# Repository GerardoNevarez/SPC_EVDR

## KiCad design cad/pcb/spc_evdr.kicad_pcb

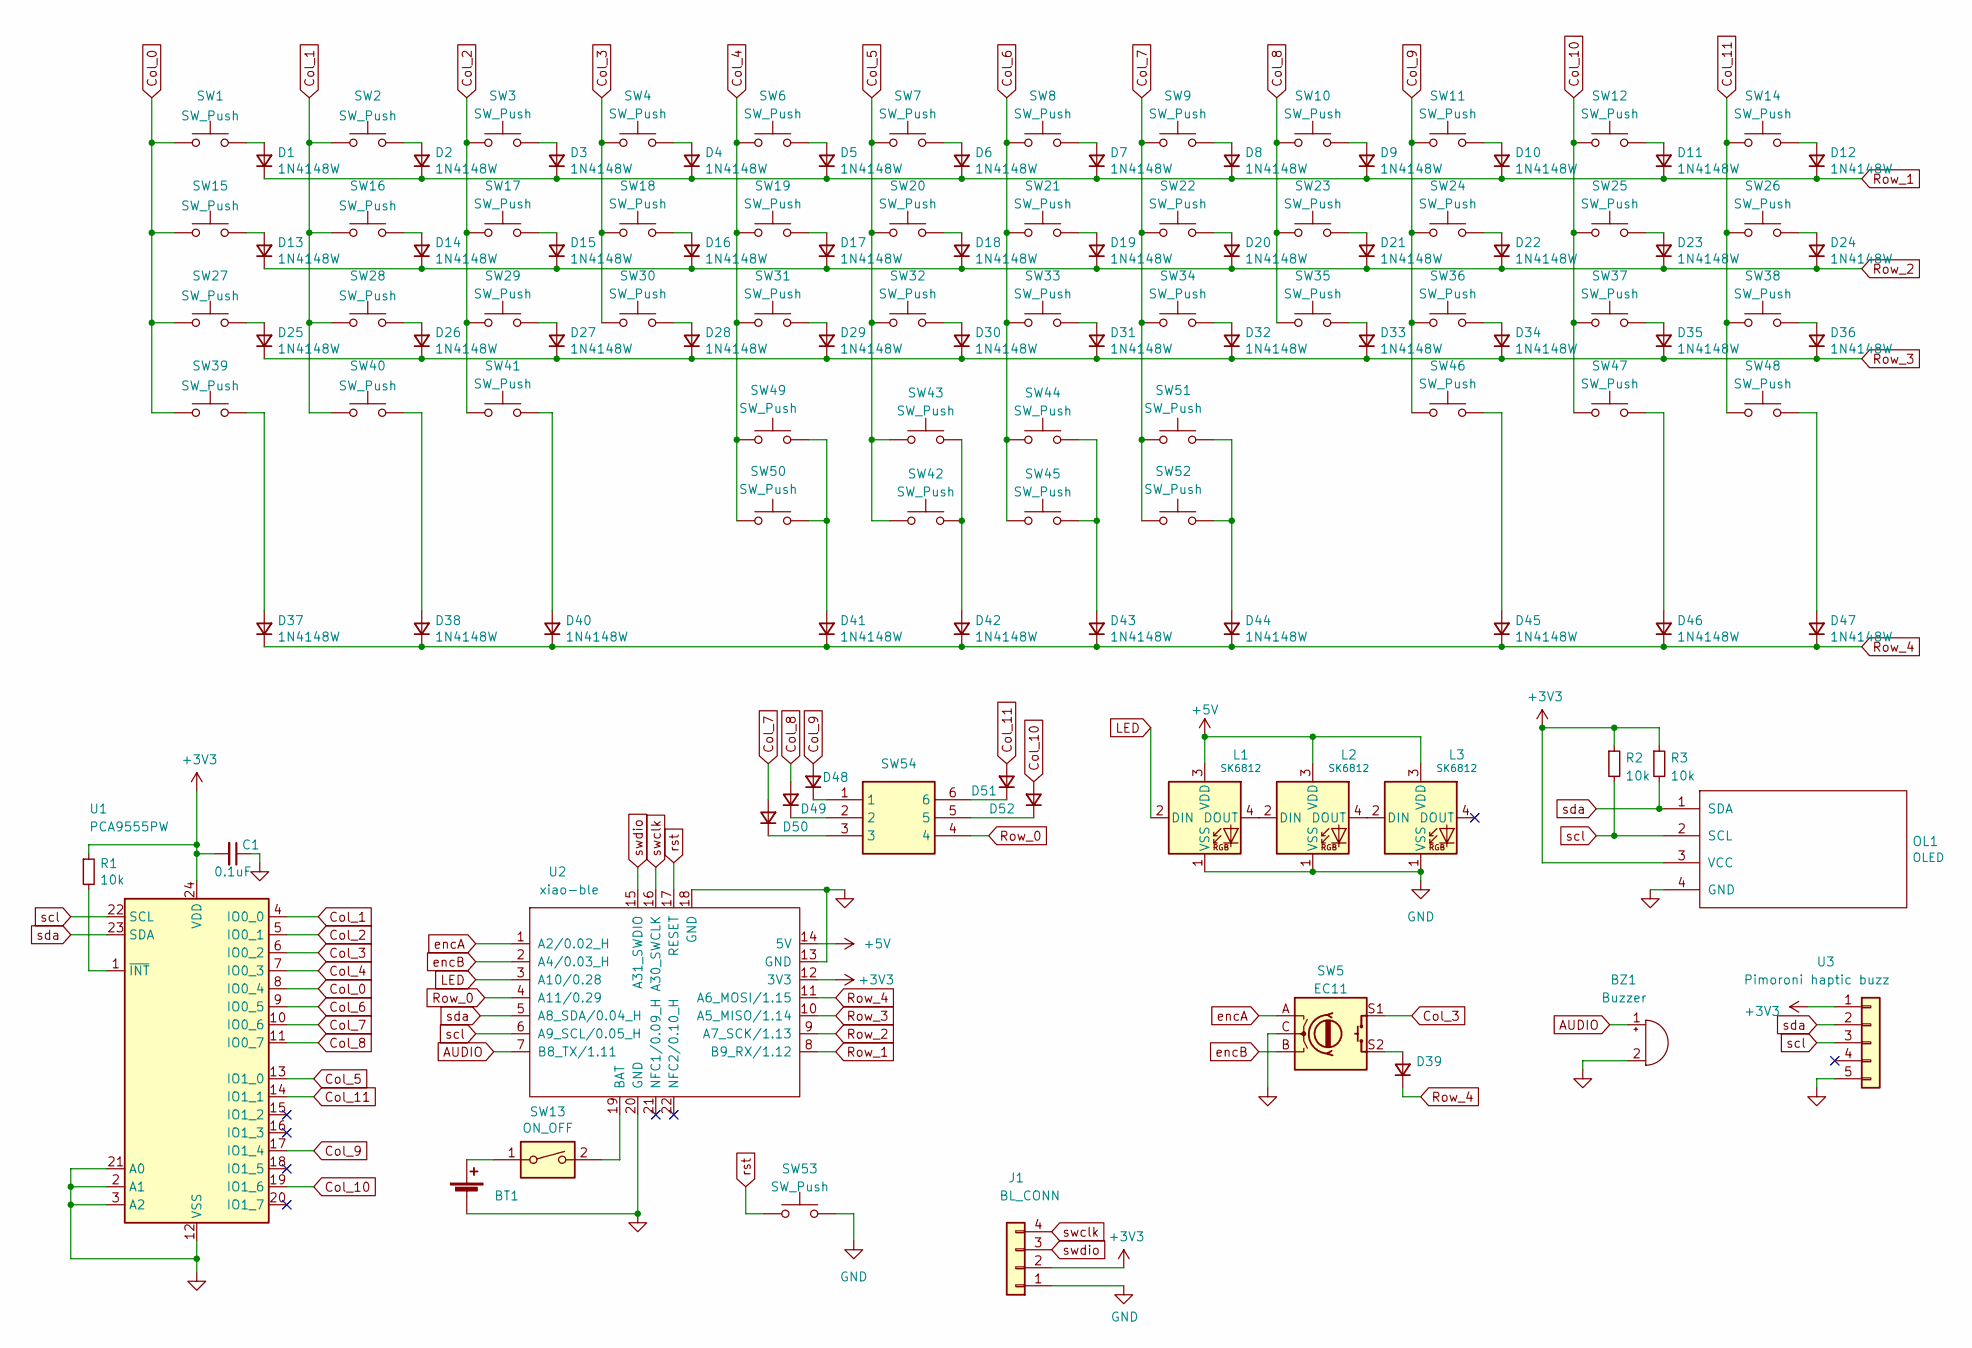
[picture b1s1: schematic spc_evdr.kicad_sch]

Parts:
BT1: Battery_Cell; Molex_PicoBlade_53048-0210_1x02_P1.25mm_Horizontal
BZ1: Buzzer; Buzzer_Mallory_AST1109MLTRQ_reversible
C1: 0.1uF; C_0805_2012Metric
D1, D2, D3, D4, D5, D6, D7, D8, D9, D10, D11, D12, D13, D14, D15, D16, D17, D18, D19, D20, D21, D22, D23, D24, D25, D26, D27, D28, D29, D30, D31, D32, D33, D34, D35, D36, D37, D38, D39, D40, D41, D42, D43, D44, D45, D46, D47, D48, D49, D50, D51, D52: 1N4148W; D_SOD-123
J1: BL_CONN; PinHeader_1x04_P2.54mm_Vertical
L1, L2, L3: SK6812; LED_SK6812_PLCC4_5.0x5.0mm_P3.2mm
OL1: OLED; OLED_1side
R1, R2, R3: 10k; R_0805_2012Metric
SW1, SW2, SW3, SW4, SW6, SW7, SW8, SW9, SW10, SW11, SW12, SW14, SW15, SW16, SW17, SW18, SW19, SW20, SW21, SW22, SW23, SW24, SW25, SW26, SW27, SW28, SW29, SW30, SW31, SW32, SW33, SW34, SW35, SW36, SW37, SW38, SW39, SW40, SW41, SW46, SW47: SW_Push; CherryMX_Hotswap
SW5: EC11; RotaryEncoder_Alps_EC11E-Switch_Vertical_H20mm-keebio_modif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
SW13: ON_OFF; switch_MSK-12C02_smd
SW42, SW45, SW49, SW51: SW_Push; Inv_CherryMX_Hotswap_1.25u
SW43, SW44, SW50, SW52: SW_Push; Inv_CherryMX_Hotswap_1.5u
SW48: SW_Push; CherryMX_1u
SW53: SW_Push; Micro_Push_Button_3x6x2.5mm
SW54: SKQUCAA010; Mouser Part Number 688-SKQUCA
U1: PCA9555PW; TSSOP-24_4.4x7.8mm_P0.65mm
U2: xiao-ble; xiao-ble-smd-cutout
U3: Pimoroni haptic buzz; Pimoroni Haptic Buzz DRV2605L Driver

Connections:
+3V3: C1.2, J1.2, OL1.3 (VCC), R1.1, R2.1, R3.1, U1.24 (VDD), U2.12 (3V3), U3.1
+5V: L1.3 (VDD), L2.3 (VDD), L3.3 (VDD), U2.14 (5V)
AUDIO: BZ1.1 (-), U2.7 (B8_TX/1.11)
Col_0: SW1.1, SW15.1, SW27.1, SW39.1, U1.8 (IO0_4)
Col_1: SW2.1, SW16.1, SW28.1, SW40.1, U1.4 (IO0_0)
Col_2: SW3.1, SW17.1, SW29.1, SW41.1, U1.5 (IO0_1)
Col_3: SW4.1, SW5.S1, SW18.1, SW30.1, U1.6 (IO0_2)
Col_4: SW6.1, SW19.1, SW31.1, SW49.1, SW50.1, U1.7 (IO0_3)
Col_5: SW7.1, SW20.1, SW32.1, SW42.1, SW43.1, U1.13 (IO1_0)
Col_6: SW8.1, SW21.1, SW33.1, SW44.1, SW45.1, U1.9 (IO0_5)
Col_7: D50.2 (A), SW9.1, SW22.1, SW34.1, SW51.1, SW52.1, U1.10 (IO0_6)
Col_8: D49.2 (A), SW10.1, SW23.1, SW35.1, U1.11 (IO0_7)
Col_9: D48.2 (A), SW11.1, SW24.1, SW36.1, SW46.1, U1.17 (IO1_4)
Col_10: D52.2 (A), SW12.1, SW25.1, SW37.1, SW47.1, U1.19 (IO1_6)
Col_11: D51.2 (A), SW14.1, SW26.1, SW38.1, SW48.1, U1.14 (IO1_1)
GND: BT1.2 (-), BZ1.2 (+), C1.1, J1.1, L1.1 (VSS), L2.1 (VSS), L3.1 (VSS), OL1.4 (GND), SW5.C, SW53.2, U1.2 (A1), U1.3 (A2), U1.12 (VSS), U1.21 (A0), U2.13 (GND), U2.18 (GND), U2.20 (GND), U3.5
LED: L1.2 (DIN), U2.3 (A10/0.28)
unnamed: BT1.1 (+), SW13.1
unnamed: D1.2 (A), SW1.2
unnamed: D2.2 (A), SW2.2
unnamed: D3.2 (A), SW3.2
unnamed: D4.2 (A), SW4.2
unnamed: D5.2 (A), SW6.2
unnamed: D6.2 (A), SW7.2
unnamed: D7.2 (A), SW8.2
unnamed: D8.2 (A), SW9.2
unnamed: D9.2 (A), SW10.2
unnamed: D10.2 (A), SW11.2
unnamed: D11.2 (A), SW12.2
unnamed: D12.2 (A), SW14.2
unnamed: D13.2 (A), SW15.2
unnamed: D14.2 (A), SW16.2
unnamed: D15.2 (A), SW17.2
unnamed: D16.2 (A), SW18.2
unnamed: D17.2 (A), SW19.2
unnamed: D18.2 (A), SW20.2
unnamed: D19.2 (A), SW21.2
unnamed: D20.2 (A), SW22.2
unnamed: D21.2 (A), SW23.2
unnamed: D22.2 (A), SW24.2
unnamed: D23.2 (A), SW25.2
unnamed: D24.2 (A), SW26.2
unnamed: D25.2 (A), SW27.2
unnamed: D26.2 (A), SW28.2
unnamed: D27.2 (A), SW29.2
unnamed: D28.2 (A), SW30.2
unnamed: D29.2 (A), SW31.2
unnamed: D30.2 (A), SW32.2
unnamed: D31.2 (A), SW33.2
unnamed: D32.2 (A), SW34.2
unnamed: D33.2 (A), SW35.2
unnamed: D34.2 (A), SW36.2
unnamed: D35.2 (A), SW37.2
unnamed: D36.2 (A), SW38.2
unnamed: D37.2 (A), SW39.2
unnamed: D38.2 (A), SW40.2
unnamed: D39.2 (A), SW5.S2
unnamed: D40.2 (A), SW41.2
unnamed: D41.2 (A), SW49.2, SW50.2
unnamed: D42.2 (A), SW42.2, SW43.2
unnamed: D43.2 (A), SW44.2, SW45.2
unnamed: D44.2 (A), SW51.2, SW52.2
unnamed: D45.2 (A), SW46.2
unnamed: D46.2 (A), SW47.2
unnamed: D47.2 (A), SW48.2
unnamed: D48.1 (K), SW54.1
unnamed: D49.1 (K), SW54.2
unnamed: D50.1 (K), SW54.3
unnamed: D51.1 (K), SW54.6
unnamed: D52.1 (K), SW54.5
unnamed: L1.4 (DOUT), L2.2 (DIN)
unnamed: L2.4 (DOUT), L3.2 (DIN)
unnamed: R1.2, U1.1 (~INT)
unnamed: SW13.2, U2.19 (BAT)
Row_0: SW54.4, U2.4 (A11/0.29)
Row_1: D1.1 (K), D2.1 (K), D3.1 (K), D4.1 (K), D5.1 (K), D6.1 (K), D7.1 (K), D8.1 (K), D9.1 (K), D10.1 (K), D11.1 (K), D12.1 (K), U2.8 (B9_RX/1.12)
Row_2: D13.1 (K), D14.1 (K), D15.1 (K), D16.1 (K), D17.1 (K), D18.1 (K), D19.1 (K), D20.1 (K), D21.1 (K), D22.1 (K), D23.1 (K), D24.1 (K), U2.9 (A7_SCK/1.13)
Row_3: D25.1 (K), D26.1 (K), D27.1 (K), D28.1 (K), D29.1 (K), D30.1 (K), D31.1 (K), D32.1 (K), D33.1 (K), D34.1 (K), D35.1 (K), D36.1 (K), U2.10 (A5_MISO/1.14)
Row_4: D37.1 (K), D38.1 (K), D39.1 (K), D40.1 (K), D41.1 (K), D42.1 (K), D43.1 (K), D44.1 (K), D45.1 (K), D46.1 (K), D47.1 (K), U2.11 (A6_MOSI/1.15)
encA: SW5.A, U2.1 (A2/0.02_H)
encB: SW5.B, U2.2 (A4/0.03_H)
rst: SW53.1, U2.17 (RESET)
scl: OL1.2 (SCL), R2.2, U1.22 (SCL), U2.6 (A9_SCL/0.05_H), U3.3
sda: OL1.1 (SDA), R3.2, U1.23 (SDA), U2.5 (A8_SDA/0.04_H), U3.2
swclk: J1.4, U2.16 (A30_SWCLK)
swdio: J1.3, U2.15 (A31_SWDIO)

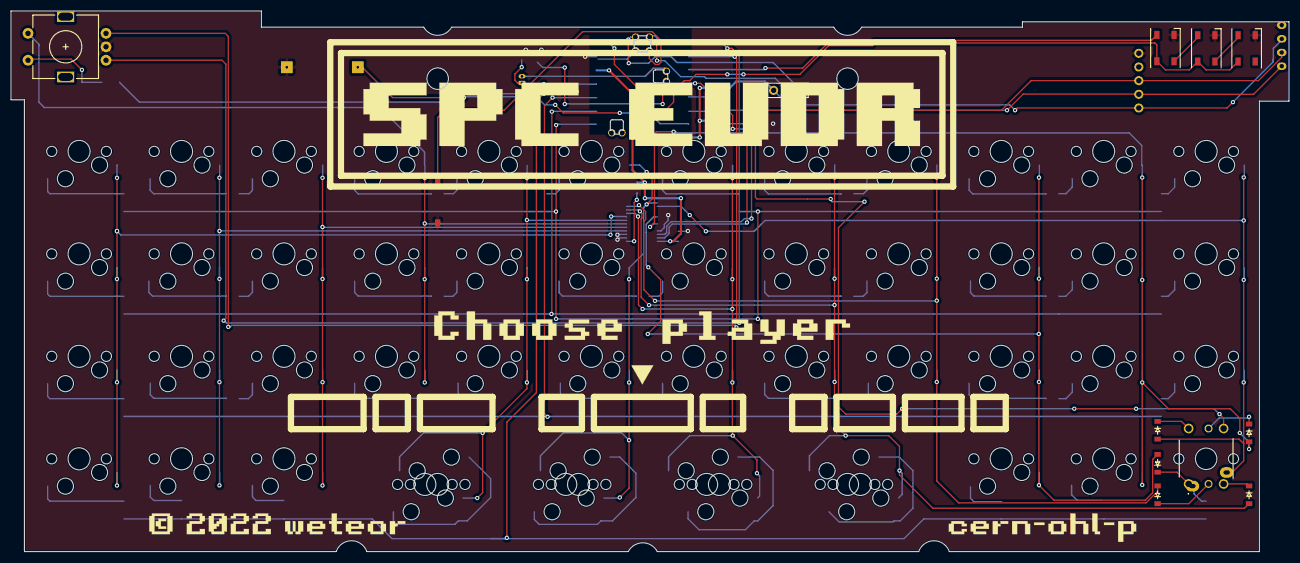
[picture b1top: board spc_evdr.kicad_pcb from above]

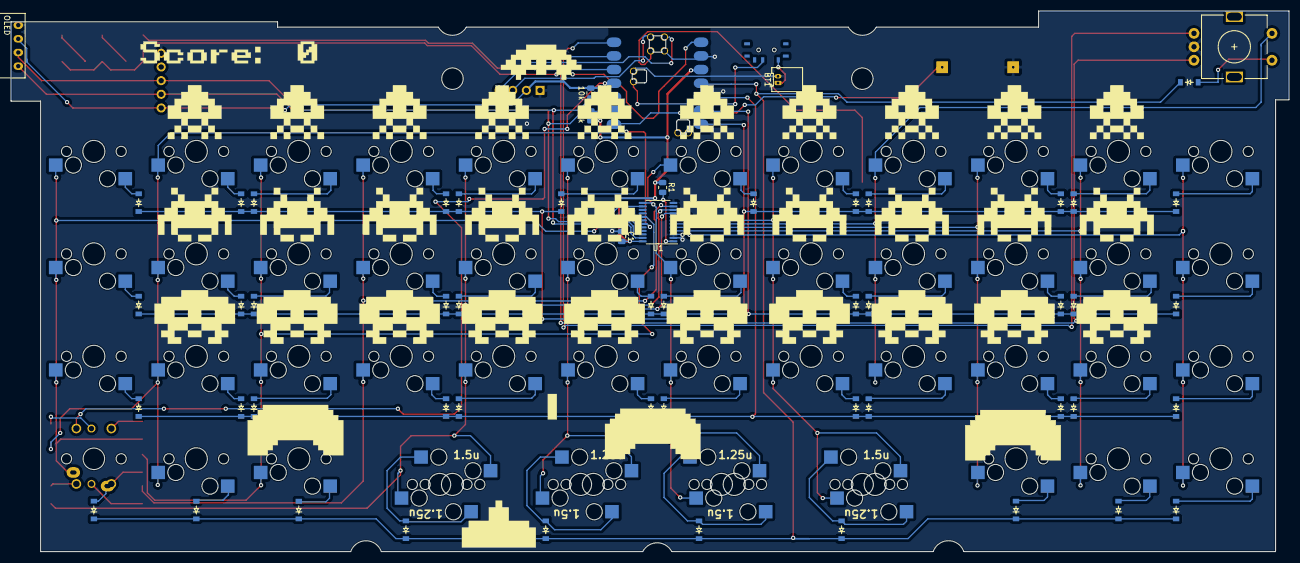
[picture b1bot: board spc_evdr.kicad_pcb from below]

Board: 2 copper layers, 237.6 x 100.5 mm, 120 parts (57 on the bottom side), 86 nets.

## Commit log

2023-03-16 added a whole lot of peripherals
2023-03-16 fix wire disconnect in matrix
2023-03-16 track nudging
2023-03-16 more hand soldering space around switch
2023-03-22 adding 12 col cad and gerbers
2023-03-22 12 col kicad files
2023-03-23 adding case files
2023-04-08 reorganized and fix silkscreens
